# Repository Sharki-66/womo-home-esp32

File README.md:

# WoMo Home ESP32 – Bordcomputer für's Wohnmobil

> Alle wichtigen Betriebsdaten auf einen Blick – immer wissen, was im Fahrzeug los ist.

## 🚐 Worum geht es?

Wer mit dem Wohnmobil unterwegs ist, kennt das Problem: Wie viel Gas ist noch in der Flasche? Reicht der Strom? Ist der Frischwassertank bald leer? Wie kalt wird es draußen über Nacht? Die serienmäßigen Anzeigen im Fahrzeug sind oft ungenau, schlecht ablesbar oder schlicht nicht vorhanden.

**WoMo Home** ersetzt das klassische EBL-Panel (LT 45x) durch ein selbstgebautes System, das alle Betriebsdaten des Wohnmobils erfasst, intelligent aufbereitet und auf einem 7-Zoll-Touchdisplay darstellt – jederzeit aktuell, übersichtlich und von überall im Fahrzeug erreichbar.

## 🎯 Was wird überwacht?

### Energie
- **Bordbatterie & Starterbatterie** – Spannung, Ladezustand
- **Landstrom** – Erkennung, ob 230V angeschlossen sind
- **12V-Bordnetz** – Ein/Aus per Touch, Übersicht aller Verbraucher

### Gas
- **Füllstandsmessung per Waage** – Zwei Gasflaschen, Anzeige in kg und Prozent
- **Verbrauchsberechnung** – Hochrechnung „Wie lange reicht das Gas noch?" auf Basis der letzten Stunden
- **Flaschenwechsel-Erkennung** – Automatisches Zurücksetzen beim Tausch

### Wasser
- **Frischwasser** und **Grauwasser** – Pegelstand in Prozent und Litern
- **Verbrauchstrend** – Restlaufzeit-Prognose

### Klima & Umgebung
- **Innenraumklima** – Temperatur, Luftfeuchte, Luftqualität (IAQ)
- **Außenklima** – Temperatur, Luftfeuchte, Luftdrucktrend
- **Wettervorhersage** – (todo) Aktuelles Wetter und 3-Tage-Prognose vom Internet
- **Unwetterwarnungen** – Eigene Auswertung der Open-Meteo-Vorhersage nach den Warnkriterien des DWD (Wind, Starkregen, Dauerregen, Schnee, Gewitter, Glatteis, Frost, Hitze), weltweit, keine amtliche Warnung

### Navigation & Lage
- **GPS-Position** – Standort, Geschwindigkeit, Höhe über dem Router
- **Kompass & Neigung** – Fahrzeugausrichtung, Pitch/Roll (Nivellierung beim Aufstellen)
- **Reverse Geocoding** – Automatische Ortsbestimmung (z. B. „Berchtesgaden, Bayern")

### Konnektivität
- **WLAN** – Verbindung zu Campingplatz-Netzen oder Hotspots
- **LTE** – Mobiles Internet über den Router
- **Hotspot** – Eigenes WLAN für alle Geräte im Fahrzeug
- Steuerung und Statusanzeige direkt am Touchscreen

## 🏗️ Wie ist das System aufgebaut?

Das System besteht aus drei Komponenten:

**Sensorboard** – Ein kleiner Mikrocontroller, der sämtliche Sensoren und Aktoren bedient: Waagen, Temperatursensoren, Batteriespannungen, Tankpegel, Kompass. Er sitzt versteckt hinter dem EBL-Schrank und ersetzt dort das originale Anzeigepanel.

**Touchdisplay** – Ein 7-Zoll-Farbbildschirm mit Touch, eingebaut an einer gut sichtbaren Stelle. Hier laufen alle Informationen zusammen und werden grafisch aufbereitet. Über den Touchscreen lassen sich auch Funktionen steuern (Bordnetz ein/aus, Radio, WLAN).

**Router** – Hier ein Teltonika RUTX11 sorgt für die Verbindung zur Außenwelt: LTE-Internet unterwegs, WLAN auf dem Campingplatz, GPS-Ortung und ein eigener Hotspot für Laptops und Smartphones an Bord. Wurde gewählt wegen der Anschlußmöglichkeiten der Antennen auf dem Womo Dach.

Sensorboard und Display kommunizieren drahtlos per ESP-NOW (direkt zwischen den beiden ESP32, ohne Router).

## 💡 Warum selbst bauen?

- **Genauigkeit** – Die Gasflaschen-Waage zeigt den Füllstand in Gramm statt „irgendwo zwischen halb und voll". Die Tankpegel werden kalibriert statt geschätzt.
- **Alles an einem Ort** – Kein Aufstehen mehr, um am EBL-Panel nachzuschauen. Kein separates Thermometer, keine Extra-App für den Router.
- **Intelligente Prognosen** – Das System rechnet mit: Wie lange reicht das Gas bei aktuellem Verbrauch? Wann ist der Tank leer? Wie entwickelt sich der Luftdruck?
- **Offenes System** – Komplett Open Source auf ESP32-Basis. Erweiterbar, anpassbar, reparierbar. Kein Cloud-Zwang, keine Abo-Kosten.
- **Robustheit** – Industriekomponenten (Metallgehäuse-Router), für den 12V-Betrieb ausgelegt. Funktioniert auch ohne Internet.
- **Weil es Spass macht und so noch nicht gibt.**

## 📁 Projektstruktur

```
womo-home-esp32/
├── firmware/
│   ├── display/            ← Firmware für das Touchdisplay
│   └── sensorboard/        ← Firmware für das Sensorboard
├── hardware/
│   ├── schematics/          ← Schaltpläne
│   └── datasheets/          ← Datenblätter der Komponenten
├── docs/                    ← Ausführliche Dokumentation
└── tests/                   ← Einzelne Hardware-Tests
```

Technische Details (Pinbelegungen, Protokoll, Build-Anleitung) finden sich in den jeweiligen Unterordnern und in [docs/README.md](docs/README.md).

## 🔧 Entwicklung

Das Projekt nutzt das [Espressif ESP-IDF](https://docs.espressif.com/projects/esp-idf/en/stable/esp32s3/get-started/) Framework. Für jeden Firmware-Teil gibt es einen eigenen VS Code Workspace mit vorkonfigurierten Build/Flash/Monitor-Tasks:

- `womo-sensor.code-workspace` – Sensorboard-Entwicklung
- `womo-display.code-workspace` – Display-Entwicklung

**!!! Der gesammte Code wurde im Vibe Coding erzeugt !!!**

## ⚠️ Haftungsausschluss

WoMo Home ist ein privates Hobbyprojekt. Schaltpläne, Firmware und Anleitungen werden ohne jede Gewähr bereitgestellt. **Nachbau, Einbau und Nutzung erfolgen ausschließlich auf eigene Gefahr.**

- Eingriffe in die Fahrzeugelektrik (12-V-Bordnetz, EBL, Batterien) und Arbeiten im Umfeld der Gasanlage nur mit ausreichender Sachkunde. Sie können Garantie- oder Gewährleistungsansprüche gegenüber Fahrzeug- oder Aufbauhersteller gefährden.
- WoMo Home ersetzt keine vorgeschriebenen Prüfungen (z. B. Gasprüfung nach DVGW G 607) und keine Sicherheitseinrichtungen. Messwerte können ungenau sein oder ausfallen.
- Für Schäden an Fahrzeugen, Geräten, Batterien oder sonstigem Eigentum sowie für Folgeschäden wird – soweit gesetzlich zulässig – keine Haftung übernommen. Unberührt bleiben die Haftung für Vorsatz und grobe Fahrlässigkeit, für Schäden an Leben, Körper oder Gesundheit, nach dem Produkthaftungsgesetz sowie gesetzliche Gewährleistungsrechte bei gekauften Produkten.

Vollständiger Text im Impressum der Website ([website/src/pages/impressum.astro](website/src/pages/impressum.astro), Abschnitt „Haftungsausschluss für Nachbau und Nutzung“).

## 📜 Lizenz

Privates Projekt. Siehe [LICENSE](LICENSE).

## 📸 Aufbau-Fotos (Feb 2026)

| Display (Vorderseite) | Sensorboard (Rückseite) |
|---|---|
|  |  |

## 🖥️ Display-Screenshots

| Nacht-Ansicht | GPS |
|---|---|
|  |  |

| Wetter | Einstellungen |
|---|---|
|  |  |

| Gas wechseln | Nivellieren |
|---|---|
|  |  |

| Nivellieren |
|---|
|  |

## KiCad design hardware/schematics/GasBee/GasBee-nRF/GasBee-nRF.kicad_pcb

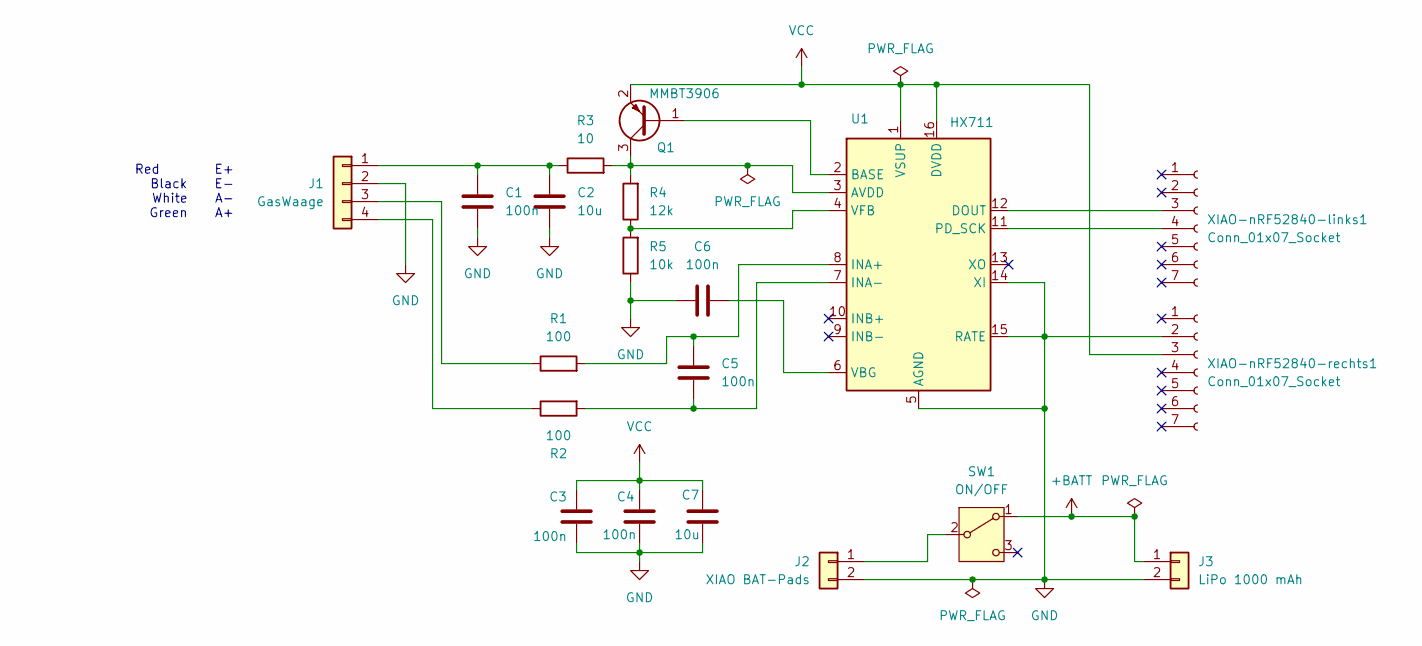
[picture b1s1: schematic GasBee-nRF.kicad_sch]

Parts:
C1, C3, C4, C5, C6: 100n; C_0603_1608Metric
C2, C7: 10u; C_0603_1608Metric
J1: GasWaage; JST_XH_S4B-XH-A_1x04_P2.50mm_Horizontal
J2: XIAO BAT-Pads; PinHeader_1x02_P2.54mm_Vertical
J3: LiPo 1000 mAh; JST_GH_SM02B-GHS-TB_1x02-1MP_P1.25mm_Horizontal
Q1: MMBT3906; SOT-23
R1, R2: 100; R_0603_1608Metric
R3: 10; R_0603_1608Metric
R4: 12k; R_0603_1608Metric
R5: 10k; R_0603_1608Metric
SW1: ON/OFF; SW_SPDT_CK_JS102011SAQN
U1: HX711; SOIC-16_3.9x9.9mm_P1.27mm
XIAO-nRF52840-links1, XIAO-nRF52840-rechts1: Conn_01x07_Socket; PinSocket_1x07_P2.54mm_Vertical

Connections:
+BATT: J3.1, SW1.1 (A)
GND: C1.2, C2.2, C3.1, C4.1, C6.1, C7.1, J1.2, J2.2, J3.2, R5.1, U1.5 (AGND), U1.14 (XI), U1.15 (RATE), XIAO-nRF52840-rechts1.2
unnamed: C1.1, C2.1, J1.1, R3.1
unnamed: J1.3, R1.1
unnamed: J1.4, R2.1
unnamed: J2.1, SW1.2 (B)
unnamed: Q1.1 (B), U1.2 (BASE)
unnamed: Q1.3 (C), R3.2, R4.2, U1.3 (AVDD)
unnamed: U1.12 (DOUT), XIAO-nRF52840-links1.3
unnamed: C5.2, R1.2, U1.8 (INA+)
unnamed: C5.1, R2.2, U1.7 (INA-)
unnamed: U1.11 (PD_SCK), XIAO-nRF52840-links1.4
unnamed: C6.2, U1.6 (VBG)
unnamed: R4.1, R5.2, U1.4 (VFB)
VCC: C3.2, C4.2, C7.2, Q1.2 (E), U1.1 (VSUP), U1.16 (DVDD), XIAO-nRF52840-rechts1.3

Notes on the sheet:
Red E+ Black E- White A- Green A+

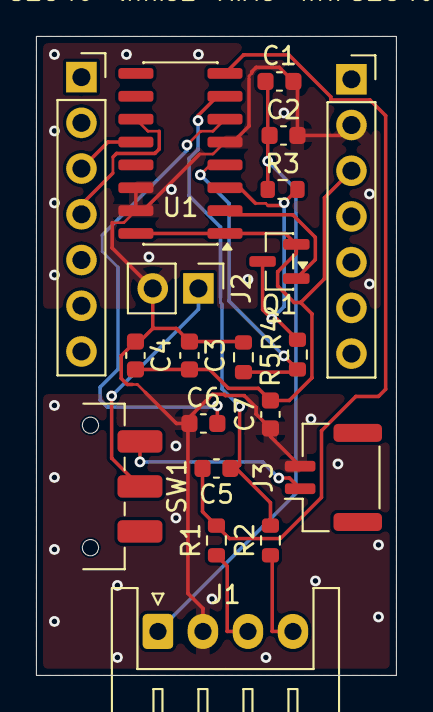
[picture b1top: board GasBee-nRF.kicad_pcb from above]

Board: 2 copper layers, 20.0 x 35.5 mm, 20 parts (0 on the bottom side), 15 nets.

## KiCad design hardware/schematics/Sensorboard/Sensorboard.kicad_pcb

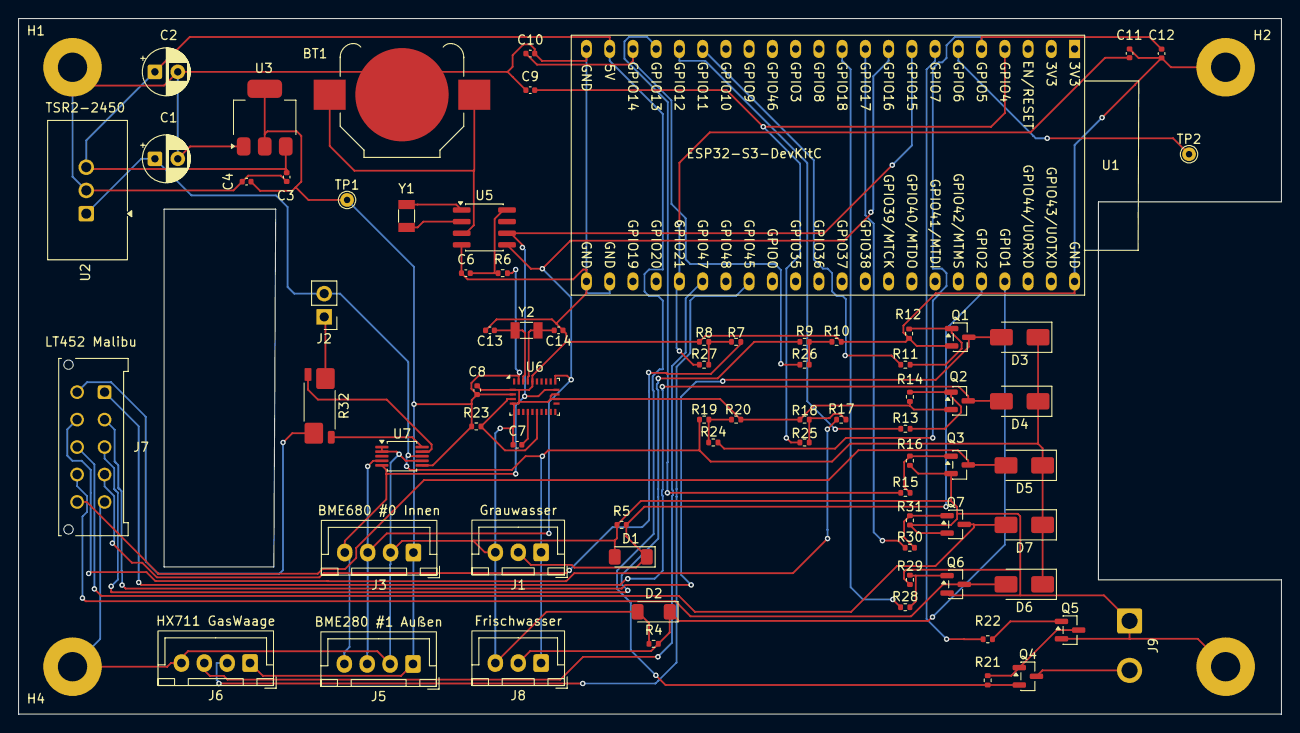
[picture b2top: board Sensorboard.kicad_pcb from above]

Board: 2 copper layers, 138.0 x 76.0 mm, 79 parts (0 on the bottom side), 53 nets.

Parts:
BT1: Battery_Cell; BatteryHolder_Keystone_3000_1x12mm
C1, C2: 100uF; CP_Radial_D5.0mm_P2.50mm
C3, C4, C6: 10uF; C_0402_1005Metric
C7: 1uF; C_0402_1005Metric
C8, C9, C10, C11, C12: 100nF; C_0402_1005Metric
C13, C14: 12pF; C_0402_1005Metric
D1, D2: BZV55B3V3; D_MiniMELF
D3, D4, D5, D6, D7: SS14; D_SMA
H1, H2, H3, H4: MountingHole_Pad; MountingHole_3.2mm_M3_Pad
J1: Grauwasser; JST_XH_B3B-XH-A_1x03_P2.50mm_Vertical
J2: Switch/Solder Jumper; PinHeader_1x02_P2.54mm_Vertical
J3: BME680 #0 Innen; JST_XH_B4B-XH-A_1x04_P2.50mm_Vertical
J5: BME280 #1 Außen; JST_XH_B4B-XH-A_1x04_P2.50mm_Vertical
J6: HX711 GasWaage; JST_XH_B4B-XH-A_1x04_P2.50mm_Vertical
J7: LT452 Malibu; Molex_Micro-Fit_3.0_43045-1012_2x05_P3.00mm_Vertical
J8: Frischwasser; JST_XH_B3B-XH-A_1x03_P2.50mm_Vertical
J9: USB Power; SolderWire-1sqmm_1x02_P5.4mm_D1.4mm_OD2.7mm
Q1, Q2, Q3, Q6, Q7: IRLML2244; SOT-23
Q4: AO3401A; SOT-23
Q5: 2N7002; SOT-23
R4, R5, R7, R9, R12, R14, R16, R17, R19, R21, R29, R31: 100k; R_0402_1005Metric
R6, R24, R25, R26, R27: 1k; R_0402_1005Metric
R8, R10, R18, R20: 22k; R_0402_1005Metric
R11, R13, R15, R28, R30: 100; R_0402_1005Metric
R22, R23: 10k; R_0402_1005Metric
R32: 10m; R_Shunt_Vishay_WSK2512_6332Metric_T1.19mm
TP1: Power 3.3 Test; TestPoint_THTPad_D1.5mm_Drill0.7mm
TP2: Display Touch; TestPoint_THTPad_D1.5mm_Drill0.7mm
U1: ESP32-S3-DevKitC; ESP32-S3-DevKitC-Heemol
U2: TSR2-2450; Converter_DCDC_TRACO_TSR2-xxxx_THT
U3: LDL1117S33R; SOT-223-3_TabPin2
U5: PCF8523T; SOIC-8_3.9x4.9mm_P1.27mm
U6: BNO055; LGA-28_5.2x3.8mm_P0.5mm
U7: INA226; VSSOP-10_3x3mm_P0.5mm
Y1, Y2: 32.768; Crystal_SMD_3215-2Pin_3.2x1.5mm

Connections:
+3.3V: C4.1, C8.1, J3.1, J5.1, J6.1, R6.2, R23.1, TP1.1, U3.2 (VO), U6.3 (VDD), U6.28 (VDDIO), U7.6 (VS)
+5V: C2.1, C3.1, Q4.2 (S), R21.1, U1.21 (5V), U2.3 (Vout), U3.3 (VI)
+12V: C1.1, D3.1 (K), D4.1 (K), D5.1 (K), D6.1 (K), D7.1 (K), J1.1, J2.2, J8.1, R19.1, U2.1 (Vin), U7.8 (Vbus)
/12V - AUS: D4.2 (A), J7.1, Q2.3 (D)
/12V - EIN: D3.2 (A), J7.2, Q1.3 (D)
/12V - Kontrolle: J7.3, R9.1
/I2C SCL: J3.4, J5.4, U1.8 (GPIO15/ADC2_CH4/32K_P), U5.6 (SCL), U6.19 (COM1), U7.5 (SCL)
/I2C SDA: J3.3, J5.3, U1.9 (GPIO16/ADC2_CH5/32K_N), U5.5 (SDA), U6.20 (COM0), U7.4 (SDA)
/Licht: D7.2 (A), J7.8, Q7.3 (D)
/Multimedia: D5.2 (A), J7.10, Q3.3 (D)
/Netz: J7.4, R7.1
/Pumpe: D6.2 (A), J7.9, Q6.3 (D)
/SB: J7.7, R17.1
/WB: J7.6, R32.4
GND: BT1.2 (-), C1.2, C2.2, C3.2, C4.2, C6.1, C7.2, C8.2, C9.1, C10.1, C11.1, C12.1, C13.2, C14.1, D1.2 (A), D2.2 (A), H1.1, H2.1, H3.1, H4.1, J1.3, J3.2, J5.2, J6.4, J7.5, J8.3, J9.1, Q1.2 (S), Q2.2 (S), Q3.2 (S), Q5.2 (S), Q6.2 (S), Q7.2 (S), R4.2, R5.2, R8.2, R10.2, R12.1, R14.1, R16.1, R18.2, R20.2, R29.1, R31.1, U1.22 (GND), U1.23 (GND), U1.24 (GND), U1.44 (GND), U2.2 (GND), U3.1 (GND), U5.4 (VSS), U6.2 (GND), U6.5 (PS1), U6.6 (PS0), U6.17 (COM3), U6.18 (COM2), U6.25 (GNDIO), U7.1 (A1), U7.2 (A0), U7.7 (GND)
unnamed: BT1.1 (+), U5.3 (VBAT)
unnamed: D1.1 (K), J1.2, R5.1, U1.40 (GPIO2/ADC1_CH1)
unnamed: D2.1 (K), J8.2, R4.1, U1.41 (GPIO1/ADC1_CH0)
unnamed: J2.1, R32.1
unnamed: J6.2, U1.30 (GPIO45)
unnamed: J6.3, U1.28 (GPIO47)
unnamed: J9.2, Q4.3 (D)
unnamed: Q1.1 (G), R11.2, R12.2
unnamed: Q2.1 (G), R13.2, R14.2
unnamed: Q3.1 (G), R15.2, R16.2
unnamed: Q4.1 (G), Q5.3 (D), R21.2
unnamed: Q5.1 (G), R22.1
unnamed: Q6.1 (G), R28.2, R29.2
unnamed: Q7.1 (G), R30.2, R31.2
unnamed: R9.2, R10.1, R26.2
unnamed: R17.2, R18.1, R25.2
unnamed: R19.2, R20.1, R24.1
unnamed: R7.2, R8.1, R27.2
unnamed: C9.2, R25.1, U1.4 (GPIO4/ADC1_CH3)
unnamed: C12.2, R24.2, U1.5 (GPIO5/ADC1_CH4)
unnamed: TP2.1, U1.6 (GPIO6/ADC1_CH5)
unnamed: R22.2, U1.7 (GPIO7/ADC1_CH6)
unnamed: R11.1, U1.17 (GPIO11/ADC2_CH0)
unnamed: R13.1, U1.18 (GPIO12/ADC2_CH1)
unnamed: R15.1, U1.19 (GPIO13/ADC2_CH2)
unnamed: C10.2, R26.1, U1.20 (GPIO14/ADC2_CH3)
unnamed: R30.1, U1.10 (GPIO17/ADC2_CH6)
unnamed: R28.1, U1.11 (GPIO18/ADC2_CH7)
unnamed: C11.2, R27.1, U1.27 (GPIO21)
unnamed: U5.1 (OSCI), Y1.2
unnamed: U5.2 (OSCO), Y1.1
unnamed: C6.2, R6.1, U5.8 (VDD)
unnamed: C7.1, U6.9 (CAP)
unnamed: C13.1, U6.27 (XIN32), Y2.2
unnamed: C14.2, U6.26 (XOUT32), Y2.1
unnamed: R23.2, U6.4 (~BOOT_LOAD_PIN), U6.11 (~RESET)
unnamed: R32.3, U7.10 (Vin+)
unnamed: R32.2, U7.9 (Vin-)

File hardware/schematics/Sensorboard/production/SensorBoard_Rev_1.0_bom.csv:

Designator,Footprint,Quantity,Value,LCSC Part #
BT1,BatteryHolder_Keystone_3034_1x20mm,1,Battery_Cell,
"C1, C2",CP_Radial_D5.0mm_P2.50mm,2,100uF,
"C3, C4, C6",0402,3,10uF,
C5,0402,1,100nF,
"D1, D2, D3, D4, D8, D9",D_MiniMELF,6,BZV55B3V3,
"D5, D6, D7",D_DO-35_SOD27_P7.62mm_Horizontal,3,1N4148,
J1,JST_XH_B3B-XH-A_1x03_P2.50mm_Vertical,1,Grauwasser,
J2,PinHeader_1x06_P2.54mm_Vertical,1,BNO055 IMU,
J3,JST_XH_B4B-XH-A_1x04_P2.50mm_Vertical,1,BME680 #0 Innen,
J4,JST_XH_B2B-XH-A_1x02_P2.50mm_Vertical,1,RS485,
J5,JST_XH_B4B-XH-A_1x04_P2.50mm_Vertical,1,BME680 #1 Außen,
J6,JST_XH_B4B-XH-A_1x04_P2.50mm_Vertical,1,HX711 GasWaage,
J7,Molex_Micro-Fit_3.0_43045-1012_2x05_P3.00mm_Vertical,1,LT452 Malibu,
J8,JST_XH_B3B-XH-A_1x03_P2.50mm_Vertical,1,Frischwasser,
"Q1, Q2, Q3",SOT-23,3,BSS138,
Q4,SOT-23,1,AO3401A,
"R1, R11, R13, R15, R2",0402,5,100,
"R10, R18, R20, R8",0402,4,22k,
"R12, R14, R16, R17, R19, R21, R4, R5, R7, R9",0402,10,100k,
R22,0402,1,10k,
R3,0402,1,120,
R6,0402,1,1k,
TP1,PinHeader_1x02_P2.54mm_Vertical,1,USB PWR,
TP2,TestPoint_THTPad_1.0x1.0mm_Drill0.5mm,1,Display Touch,
U1,ESP32-S3-DevKitC,1,ESP32-S3-DevKitC,
U2,Converter_DCDC_TRACO_TSR2-xxxx_THT,1,TSR2-2450,
U3,SOT-223-3_TabPin2,1,LDL1117S33R,
U4,DIP-8_W7.62mm,1,SP3485CP,
U5,SOIC-8_3.9x4.9mm_P1.27mm,1,PCF8523T,
Y1,Crystal_SMD_3215-2Pin_3.2x1.5mm,1,32.768,

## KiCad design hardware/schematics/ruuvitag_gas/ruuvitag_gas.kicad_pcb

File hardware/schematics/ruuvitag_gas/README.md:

# RuuviTag Gas (WoMoHome)

Gaswaagen-Variante des RuuviTag für das WoMoHome-ESP32-Projekt.
Fork von **RuuviTag Rev.B8** (`ruuvi/ruuvitag_hw` @ `afa1b03`), Lizenz **CC BY-SA 4.0** (von RuuviTag geerbt).

## Ziel

BLE-Beacon auf nRF52832-Basis, der zusätzlich zur Klimamessung eine
**Gasflaschen-Waage** über einen **HX711** ausliest und das Gewicht ins
BLE-Advertisement schreibt. Ersetzt mittelfristig das ESP32-C3-`GasBee`.

## Hardware

| Block | Bauteil | Schnittstelle | Status |
|---|---|---|---|
| MCU | nRF52832-QFAA | — | von B8 übernommen |
| Klima | SHTC3 | I²C (`SDA`/`SCL`), Power über `SENSOR_PWR_1` | von B8 übernommen |
| Wägung | HX711 + High-Side-Load-Switch | 3 GPIO: `DOUT`=P0.08, `PD_SCK`=P0.07, `HX711_EN`=P0.03 | **Phase 2 – geplant** |
| Wägezelle | Vollbrücke aus 4× 50 kg (extern vorkombiniert) | 4 SMD-Lötpads `E+ / E- / A+ / A-` | **Phase 2 – geplant** |
| Speisung | CR2477-Knopfzelle (Clip von B8) + 2 DNP-Pads `VBAT`/`GND` für optionalen externen Pack | — | **Phase 2 – geplant** |

**Entfällt gegenüber Rev.B8:** TMP117, DPS310, LIS2DH12 (inkl. SPI-Bus und Interrupt-Leitungen).

**Board:** 4-lagig, Außenmaße unverändert gegenüber Rev.B8 (Gehäuse wird unter die Wiegeplatte geklebt).
Antennen-Sperrfläche am Boardrand bleibt frei.

## Firmware

Eigene nRF52-Firmware (Nordic SDK / Zephyr bzw. Ruuvi-FW-Fork) – **nicht** ESP-IDF.
Separates Arbeitspaket, noch nicht begonnen.

## Verzeichnisinhalt

| Datei | Zweck |
|---|---|
| `ruuvitag_gas.sch` | Schaltplan (noch KiCad-5-Legacy, wird bei erstem Öffnen in KiCad 9 migriert) |
| `ruuvitag_gas.kicad_pcb` | Layout (KiCad-5-Format, Migration analog) |
| `ruuvitag_gas.kicad_pro` | Projektdatei |
| `ruuvitag_gas-cache.lib` | Symbol-Cache aus Rev.B8 (Migrationsquelle für nRF52832, SHTC3 usw.) |
| `sym-lib-table` / `fp-lib-table` | Bibliotheks-Tabellen (projektlokal); Footprints sind im PCB eingebettet |

## Migration nach KiCad 9 (einmalig, GUI)

1. `ruuvitag_gas.kicad_pro` in KiCad 9 öffnen.
2. Rückfrage „älteres Format" bestätigen.
3. Im **Symbol-Remap-/Rescue-Dialog** die Symbole aus `ruuvitag_gas-cache.lib` übernehmen.
4. Eeschema: **Speichern** → `ruuvitag_gas.kicad_sch` entsteht.
5. Pcbnew öffnen → **Speichern** → PCB wird ins v9-Format konvertiert
   (Hinweis „alte Zonenfüll-Strategie" ist erwartet).
6. ERC/DRC laufen lassen → das ist die saubere Ausgangsbasis für Phase 2.

## Status

- [x] **Phase 1** – Migration von Rev.B8 nach `ruuvitag_gas` (KiCad 9, unverändert)
- [x] **Phase 2a – Schaltplan** – Sensor-Rückbau (TMP117/DPS310/LIS2DH12), HX711 + Load-Switch
      (Option B), Wägezellen-Pads J1–J4, ext. Speise-Pads J5/J6 (DNP), Symbole/Footprints
      auf KiCad-Standard. ERC = 3 (alle erwartet). Details: [`PHASE2_HX711.md`](PHASE2_HX711.md) §8
- [ ] **Phase 2b – PCB** – „Update PCB from Schematic", Platzierung, 4-lagig routen, DRC
- [ ] **Phase 3** – Doku, BOM, Gerber

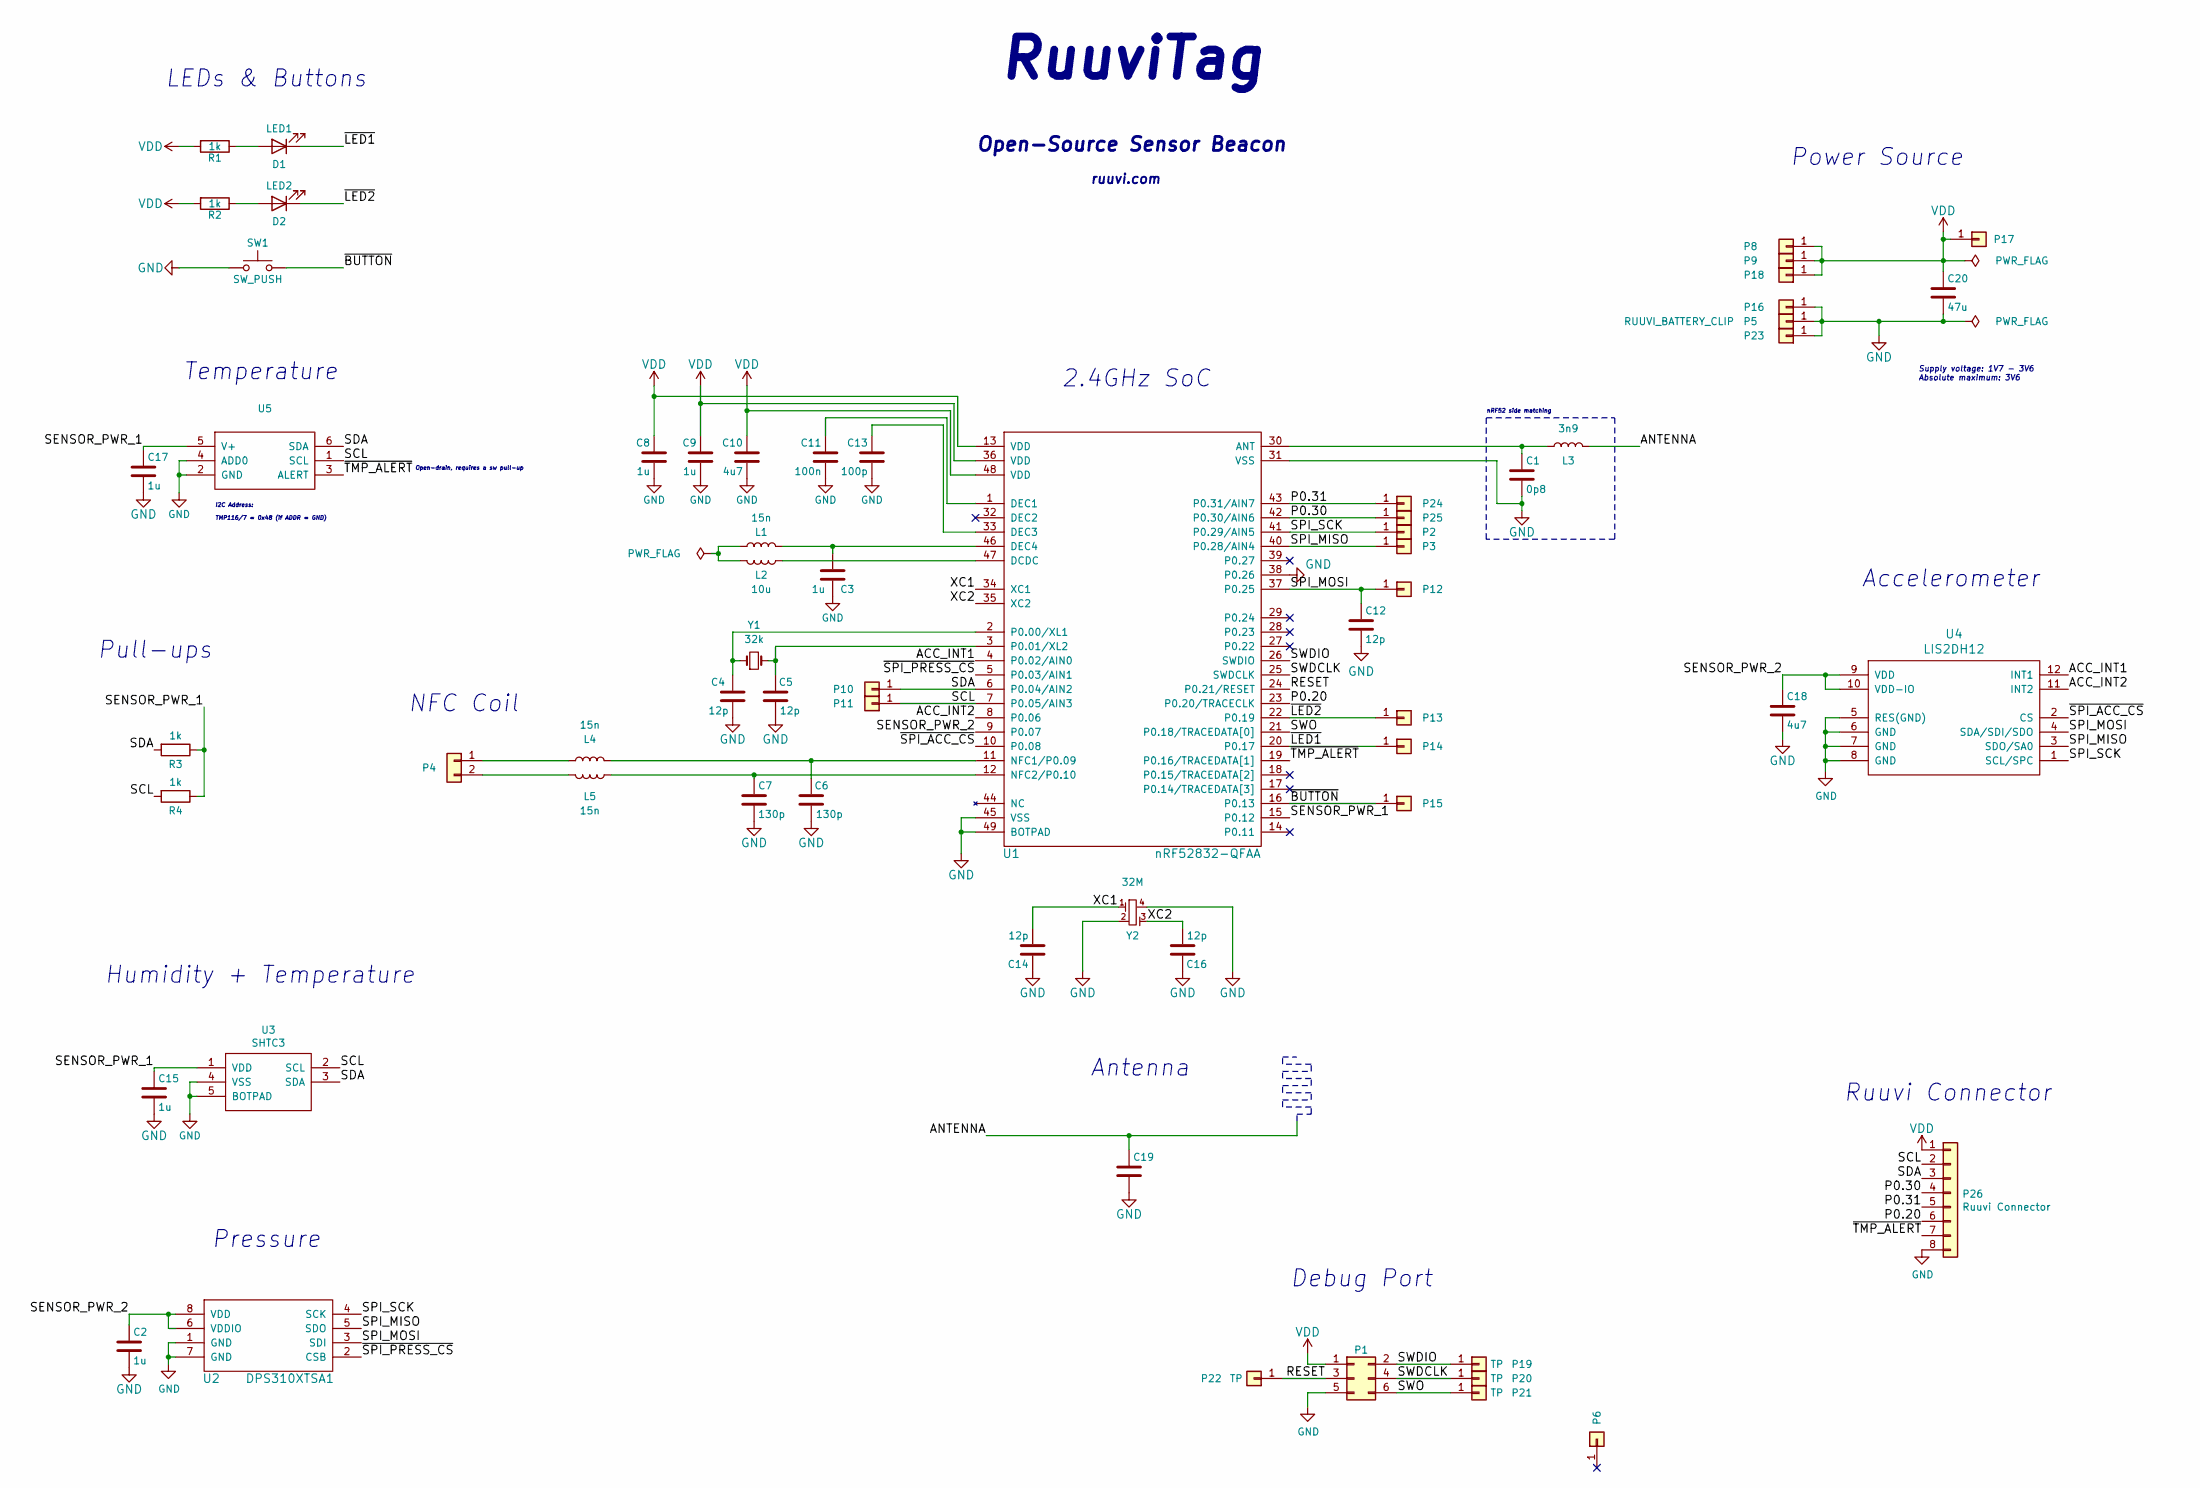
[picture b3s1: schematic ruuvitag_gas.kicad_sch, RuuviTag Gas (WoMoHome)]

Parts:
C1: 0p8; 0402_CAP
C2, C3, C8, C9, C15, C17: 1u; 0402_CAP
C4, C5, C12, C14, C16: 12p; 0402_CAP
C6, C7: 130p; 0402_CAP
C10, C18: 4u7; 0603_CAP
C11: 100n; 0402_CAP
C13: 100p; 0402_CAP
C19: 0402_CAP
C20: 47u; C_0805_2012Metric
D1: LED1; 0603_LED
D2: LED2; 0603_LED
L1, L4, L5: 15n; 0402_IND
L2: 10u; 0603_IND
L3: 3n9; 0402_IND
P1: TAGCONNECT_TC2030-MCP-NL
P2, P3, P10, P11, P12, P13, P14, P15, P16, P17, P18, P23, P24, P25: TEST_POINT_SMD_1MM
P4: NFC-B8
P5: RUUVI_BATTERY_CLIP; RUUVITAG-BAT-CONNECTOR
P6: FIDUCIAL_1MM
P8, P9: WIDE_PLATED_HOLE
P19, P20, P21, P22: TP; TEST_POINT_SMD_1MM
P26: Ruuvi Connector; RUUVI_CONNECTOR_FFC
R1, R2, R3, R4: 1k; 0402_RES
SW1: SW_PUSH; SKRKAEE010_BUTTON
U1: nRF52832-QFAA; QFN-48_6X6MM_BOTPAD
U2: DPS310XTSA1; DPS310
U3: SHTC3; DFN4_2X2MM_BOTPAD
U4: LIS2DH12; LGA12_2X2MM
U5: WSON6_NO_BOTPAD
Y1: 32k; 32X15MM_2PIN_CRYSTAL
Y2: 32M; 20X16MM_4PIN_CRYSTAL

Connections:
/ACC_INT1: U1.4 (P0.02/AIN0), U4.12 (INT1)
/ACC_INT2: U1.8 (P0.06), U4.11 (INT2)
/ANTENNA: C19.1, L3.2
/P0.20: P26.6, U1.23 (P0.20/TRACECLK)
/P0.30: P25.1, P26.4, U1.42 (P0.30/AIN6)
/P0.31: P24.1, P26.5, U1.43 (P0.31/AIN7)
/RESET: P1.3, P22.1, U1.24 (P0.21/RESET)
/SCL: P11.1, P26.2, R4.2, U1.7 (P0.05/AIN3), U3.2 (SCL), U5.1 (SCL)
/SDA: P10.1, P26.3, R3.2, U1.6 (P0.04/AIN2), U3.3 (SDA), U5.6 (SDA)
/SENSOR_PWR_1: C15.1, C17.1, R3.1, R4.1, U1.15 (P0.12), U3.1 (VDD), U5.5 (V+)
/SENSOR_PWR_2: C2.1, C18.1, U1.9 (P0.07), U2.6 (VDDIO), U2.8 (VDD), U4.9 (VDD), U4.10 (VDD-IO)
/SPI_MISO: P3.1, U1.40 (P0.28/AIN4), U2.5 (SDO), U4.3 (SDO/SA0)
/SPI_MOSI: C12.1, P12.1, U1.37 (P0.25), U2.3 (SDI), U4.4 (SDA/SDI/SDO)
/SPI_SCK: P2.1, U1.41 (P0.29/AIN5), U2.4 (SCK), U4.1 (SCL/SPC)
/SWDCLK: P1.4, P20.1, U1.25 (SWDCLK)
/SWDIO: P1.2, P19.1, U1.26 (SWDIO)
/SWO: P1.6, P21.1, U1.21 (P0.18/TRACEDATA[0])
/XC1: C14.2, U1.34 (XC1), Y2.1
/XC2: C16.2, U1.35 (XC2), Y2.3
/~BUTTON: P15.1, SW1.2, U1.16 (P0.13)
/~LED1: D1.1 (K), P14.1, U1.20 (P0.17)
/~LED2: D2.1 (K), P13.1, U1.22 (P0.19)
/~SPI_ACC_CS: U1.10 (P0.08), U4.2 (CS)
/~SPI_PRESS_CS: U1.5 (P0.03/AIN1), U2.2 (CSB)
/~TMP_ALERT: P26.7, U1.19 (P0.16/TRACEDATA[1]), U5.3 (ALERT)
GND: C1.2, C2.2, C3.2, C4.1, C5.1, C6.1, C7.2, C8.1, C9.1, C10.1, C11.1, C12.2, C13.1, C14.1, C15.2, C16.1, C17.2, C18.2, C19.2, C20.2, P1.5, P5.1, P16.1, P23.1, P26.8, SW1.1, U1.31 (VSS), U1.38 (P0.26), U1.45 (VSS), U1.49 (BOTPAD), U2.1 (GND), U2.7 (GND), U3.4 (VSS), U3.5 (BOTPAD), U4.5 (RES(GND)), U4.6 (GND), U4.7 (GND), U4.8 (GND), U5.2 (GND), U5.4 (ADD0), Y2.2, Y2.4
unnamed: C1.1, L3.1, U1.30 (ANT)
unnamed: C3.1, L1.2, U1.46 (DEC4)
unnamed: C4.2, U1.2 (P0.00/XL1), Y1.1
unnamed: C5.2, U1.3 (P0.01/XL2), Y1.2
unnamed: C6.2, L4.2, U1.11 (NFC1/P0.09)
unnamed: C7.1, L5.1, U1.12 (NFC2/P0.10)
unnamed: C11.2, U1.1 (DEC1)
unnamed: C13.2, U1.33 (DEC3)
unnamed: D1.2 (A), R1.1
unnamed: D2.2 (A), R2.1
unnamed: L1.1, L2.2
unnamed: L2.1, U1.47 (DCDC)
unnamed: L4.1, P4.1
unnamed: L5.2, P4.2
VDD: C8.2, C9.2, C10.2, C20.1, P1.1, P8.1, P9.1, P17.1, P18.1, P26.1, R1.2, R2.2, U1.13 (VDD), U1.36 (VDD), U1.48 (VDD)

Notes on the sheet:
Accelerometer
2.4GHz SoC
Open-Source Sensor Beacon
Pressure
Power Source
Pull-ups
Antenna
NFC Coil
Debug Port
ruuvi.com
RuuviTag
LEDs & Buttons
I2C Address: TMP116/7 = 0x48 (if ADDR = GND)
Supply voltage: 1V7 - 3V6 Absolute maximum: 3V6
nRF52 side matching
Temperature
Open-drain, requires a sw pull-up
Ruuvi Connector
Humidity + Temperature

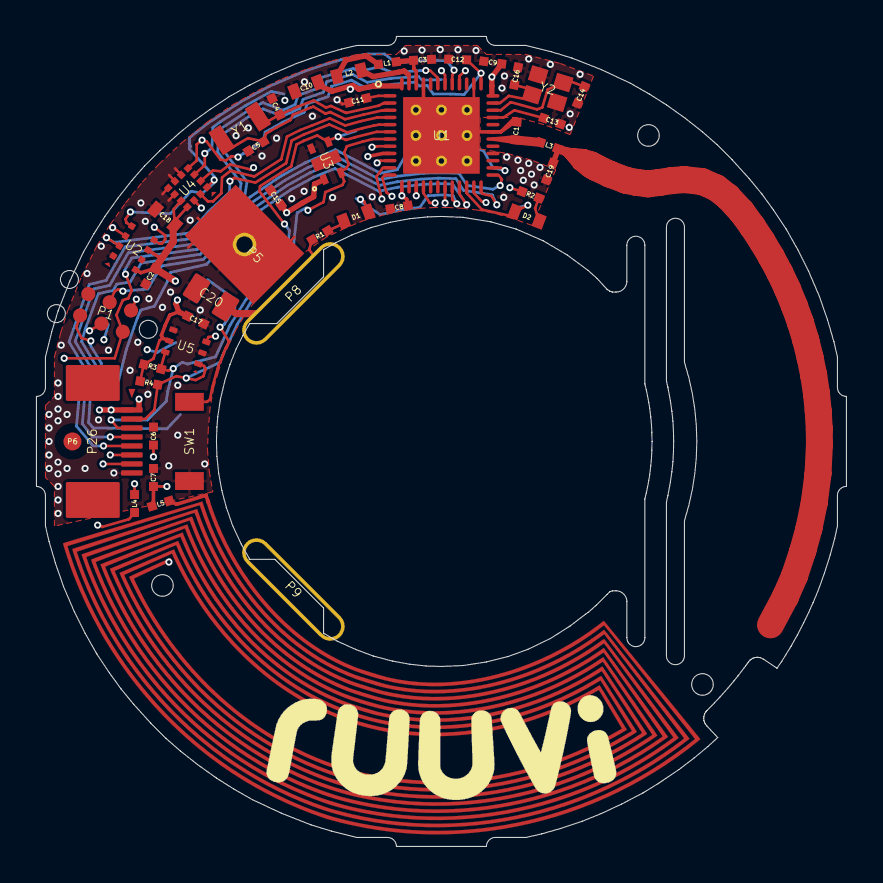
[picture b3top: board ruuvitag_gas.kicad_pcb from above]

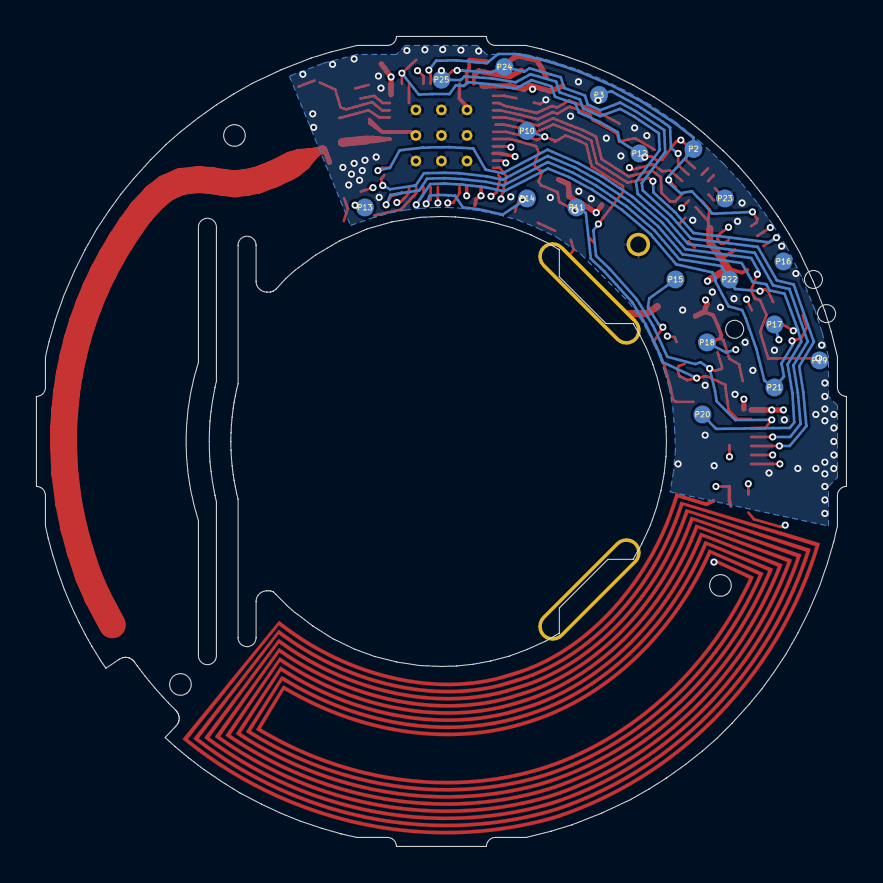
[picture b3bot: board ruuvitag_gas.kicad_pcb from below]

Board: 4 copper layers, 45.0 x 45.0 mm, 64 parts (18 on the bottom side), 41 nets.

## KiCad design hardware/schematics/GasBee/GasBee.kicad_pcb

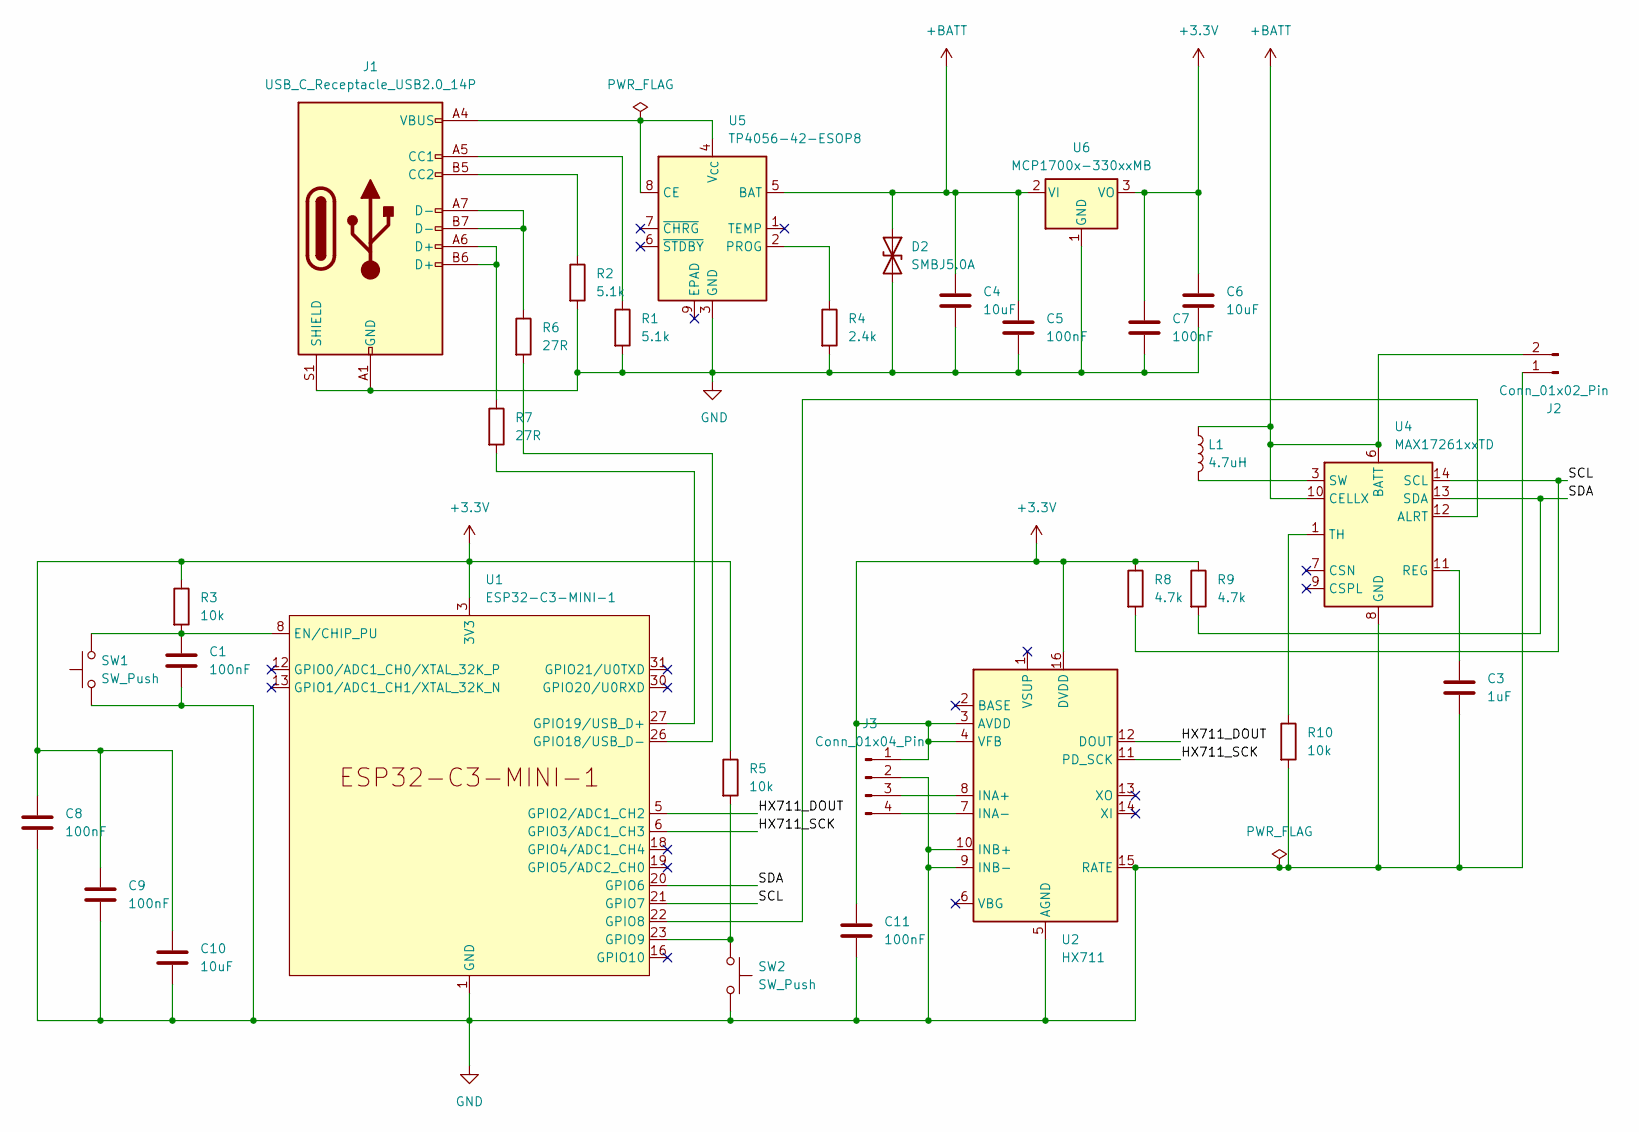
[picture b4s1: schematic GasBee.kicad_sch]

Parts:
C1, C5, C7, C8, C9, C11: 100nF; C_0402_1005Metric
C3: 1uF; C_0402_1005Metric
C4, C6, C10: 10uF; C_0805_2012Metric
D2: SMBJ5.0A; D_SOD-323
J1: USB_C_Receptacle_USB2.0_14P; USB_C_Receptacle_HRO_TYPE-C-31-M-12
J2: Conn_01x02_Pin; JST_PH_B2B-PH-K_1x02_P2.00mm_Vertical
J3: Conn_01x04_Pin; JST_XH_B4B-XH-A_1x04_P2.50mm_Vertical
L1: 4.7uH; L_0805_2012Metric
R1, R2: 5.1k; R_0402_1005Metric
R3, R5, R10: 10k; R_0402_1005Metric
R4: 2.4k; R_0402_1005Metric
R6, R7: 27R; R_0402_1005Metric
R8, R9: 4.7k; R_0402_1005Metric
SW1, SW2: SW_Push; SW_Push_1TS009xxxx-xxxx-xxxx_6x6x5mm
U1: ESP32-C3-MINI-1
U2: HX711; SOIC-16_3.9x9.9mm_P1.27mm
U4: MAX17261xxTD; TDFN-14-1EP_3x3mm_P0.4mm_EP1.78x2.35mm
U5: TP4056-42-ESOP8; SOIC-8-1EP_3.9x4.9mm_P1.27mm_EP2.41x3.3mm
U6: MCP1700x-330xxMB; SOT-23

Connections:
+3.3V: C6.1, C7.1, C8.1, C9.1, C10.1, C11.1, J3.1, R3.1, R5.1, R8.1, R9.1, U1.3 (3V3), U2.3 (AVDD), U2.4 (VFB), U2.16 (DVDD), U6.3 (VO)
+BATT: C4.1, C5.1, D2.1 (A1), J2.2, L1.1, U4.6 (BATT), U4.10 (CELLX), U5.5 (BAT), U6.2 (VI)
/HX711_DOUT: U1.5 (GPIO2/ADC1_CH2), U2.12 (DOUT)
/HX711_SCK: U1.6 (GPIO3/ADC1_CH3), U2.11 (PD_SCK)
/SCL: R8.2, U1.21 (GPIO7), U4.14 (SCL)
/SDA: R9.2, U1.20 (GPIO6), U4.13 (SDA)
GND: C1.2, C3.2, C4.2, C5.2, C6.2, C7.2, C8.2, C9.2, C10.2, C11.2, D2.2 (A2), J1.A1 (GND), J1.A12 (GND), J1.B1 (GND), J1.B12 (GND), J1.S1 (SHIELD), J2.1, J3.2, R1.2, R2.2, R4.2, R10.2, SW1.1, SW2.2, U1.1 (GND), U1.2 (GND), U1.11 (GND), U1.14 (GND), U1.36 (GND), U1.37 (GND), U1.38 (GND), U1.39 (GND), U1.40 (GND), U1.41 (GND), U1.42 (GND), U1.43 (GND), U1.44 (GND), U1.45 (GND), U1.46 (GND), U1.47 (GND), U1.48 (GND), U1.49 (GND), U1.50 (GND), U1.51 (GND), U1.52 (GND), U1.53 (GND), U2.5 (AGND), U2.9 (INB-), U2.10 (INB+), U2.15 (RATE), U4.8 (GND), U4.15 (GND), U5.3 (GND), U6.1 (GND)
unnamed: J1.A5 (CC1), R1.1
unnamed: J1.B5 (CC2), R2.1
unnamed: J1.A6 (D+), J1.B6 (D+), R7.1
unnamed: J1.A7 (D-), J1.B7 (D-), R6.1
unnamed: J3.3, U2.8 (INA+)
unnamed: J3.4, U2.7 (INA-)
unnamed: C1.1, R3.2, SW1.2, U1.8 (EN/CHIP_PU)
unnamed: U1.22 (GPIO8), U4.12 (ALRT)
unnamed: R5.2, SW2.1, U1.23 (GPIO9)
unnamed: R6.2, U1.26 (GPIO18/USB_D-)
unnamed: R7.2, U1.27 (GPIO19/USB_D+)
unnamed: C3.1, U4.11 (REG)
unnamed: L1.2, U4.3 (SW)
unnamed: R10.1, U4.1 (TH)
unnamed: J1.A4 (VBUS), J1.A9 (VBUS), J1.B4 (VBUS), J1.B9 (VBUS), U5.4 (V_{CC}), U5.8 (CE)
unnamed: R4.1, U5.2 (PROG)

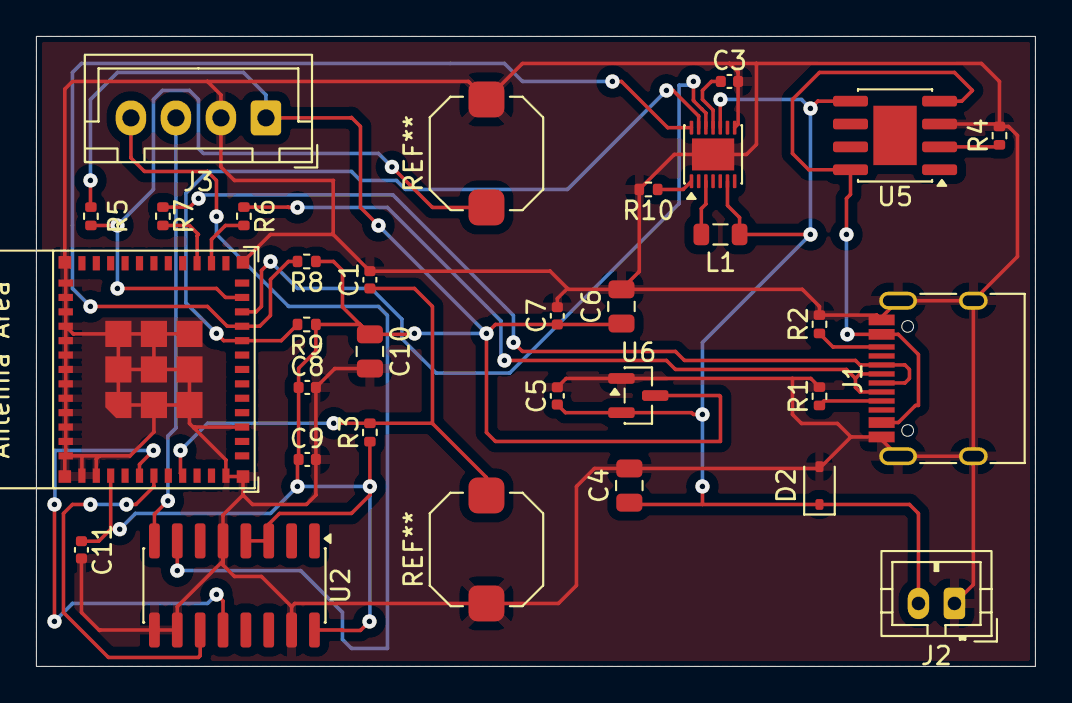
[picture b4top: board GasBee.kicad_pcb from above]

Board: 2 copper layers, 55.5 x 35.0 mm, 32 parts (0 on the bottom side), 23 nets.

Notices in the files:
hardware/schematics/ruuvitag_gas/ruuvitag_gas.kicad_sch:
License: http://creativecommons.org/licenses/by-sa/4.0/ (CC BY-SA 4.0, geerbt von RuuviTag)
